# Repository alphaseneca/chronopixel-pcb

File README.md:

# ChronoPixel PCB ⏳🔌

Hardware design repository for **ChronoPixel** — an open-source, gravity-sensing digital sand timer and smart pixel hourglass. Contains the KiCad schematics, PCB layout, manufacturing outputs, and assembly files.

---

## 📸 3D Board Previews

<div align="center">

</div>

---

## ⏳ How the Hardware Powers the Digital Sand Timer

The PCB is architected specifically around the physical interactions of a traditional hourglass:

1. **Dual Hourglass Chambers (Dual MAX7219 + 2× 8×8 LED Matrices)**:
   The two stacked LED matrices represent the upper and lower bulbs of the hourglass. Individual pixel "sand grains" trickle through the center constriction from the top chamber to accumulate in the bottom chamber.
2. **Gravity & Tilt Tracking (Bosch BMI323 6-Axis IMU)**:
   An onboard 6-axis accelerometer/gyroscope continuously measures the gravity vector. When you turn the device upside down, tilt it, or lay it flat, the physics engine responds in real-time, causing virtual sand grains to tumble and settle naturally.
3. **True Cordless Hourglass Operation (TI BQ24075)**:
   Equipped with autonomous dynamic power-path management and integrated Li-Ion/Li-Po charging. The device can be picked up, flipped, and set down on a desk cordlessly just like a classic sand glass.
4. **Time's Up Audio Alert (MLT-7525 Buzzer)**:
   An onboard SMD buzzer sounds a chime or alarm tone the instant the final grain of sand drops.
5. **Smart Connectivity (ESP-12F Wi-Fi SoC)**:
   Enables setting timer presets (e.g. 25-minute Pomodoro, 5-minute break, tea steeping, custom countdowns) via a local web interface or mobile device.

---

## ⚡ Hardware Architecture & Key Components

| Subsystem | Component | Package / Footprint | Description / Role |
| :--- | :--- | :--- | :--- |
| **Microcontroller** | **ESP-12F** | SMD Module | ESP8266 Wi-Fi SoC with on-board PCB antenna |
| **Display Drivers** | **2× MAX7219EWG** | SOIC-24 | Serially interfaced LED matrix drivers |
| **Hourglass Chambers** | **2× SZ421288N/64** | Through-hole | Stacked 8×8 LED dot matrix modules for sand grains |
| **Motion Sensor** | **BMI323** | LGA-14 | Bosch 6-axis IMU (accelerometer + gyroscope) for gravity tracking |
| **Power-Path / Charger** | **BQ24075RGTR** | QFN-16 | Dynamic power-path management & Li-Ion battery charger |
| **Voltage Regulator** | **TLV73333PDBVR** | SOT-23-5 | High-efficiency 3.3V 300mA low-dropout regulator |
| **USB Interface** | **USB Type-C (16-pin)** | SMD / Hybrid | 5V DC power & battery charging (with CC pulldowns) |
| **Battery Connector** | **SM02B-SRSS-TB** | SMD 1.0mm pitch | 2-pin JST connector for 3.7V Li-Po / Li-Ion battery |
| **Audio Feedback** | **MLT-7525** | SMD 7.5×7.5mm | Magnetic buzzer for alarm chimes when sand runs out |
| **Programming Header** | **BM06B-SRSS-TB** | SMD 1.0mm pitch | 6-pin interface (UART, RST, GPIO0, 3V3, GND) |
| **Control Switch** | **B3U-1000P** | Ultra-small SMD | Hardware input / wake tactile switch |

---

## 🔋 Power Architecture

- **Seamless Cordless & Desktop Use**: Operates cordlessly on a rechargeable 3.7V Li-Po/Li-Ion battery or plugged in over USB Type-C.
- **Dynamic Power-Path Management (TI BQ24075)**: 
  - When USB is connected, system loads are powered directly from the USB supply while simultaneously charging the battery.
  - Automatically supplements system current from the battery if load exceeds USB current limits.
  - Instantaneous, glitch-free switchover to battery power when unseated or picked up.
- **Clean 3.3V Rail**: Powered by a low-noise TI TLV73333 LDO ensuring stable power for the ESP8266 Wi-Fi bursts and low-noise readings from the BMI323 IMU.

---

## 📁 Repository Structure

```text
chronopixel-pcb/
├── chronopixel-pcb.kicad_pro    # KiCad project file
├── chronopixel-pcb.kicad_sch    # Schematic design file
├── chronopixel-pcb.kicad_pcb    # 2-layer PCB layout
├── chronopixel-pcb.kicad_prl    # KiCad local settings
├── .kiforge.json                # KiForge export configuration
└── kiforge/                     # Automated manufacturing & inspection artifacts
    ├── chronopixel-pcb_v0.1.0_gerbers.zip   # Fabrication Gerbers & drill files
    ├── chronopixel-pcb_v0.1.0_bom.csv       # Complete bill of materials
    ├── chronopixel-pcb_v0.1.0_bom_jlc.csv   # JLCPCB formatted BOM (with LCSC C-IDs)
    ├── chronopixel-pcb_v0.1.0_cpl_jlc.csv   # JLCPCB pick-and-place (CPL/POS) file
    ├── chronopixel-pcb_v0.1.0_ibom.html     # Interactive HTML BOM for easy hand assembly
    ├── chronopixel-pcb_v0.1.0_sch.pdf       # Printable schematic PDF
    ├── chronopixel-pcb_v0.1.0.step          # Complete 3D STEP CAD model
    ├── chronopixel-pcb_v0.1.0_3d_front.png  # 3D render front
    └── chronopixel-pcb_v0.1.0_3d_back.png   # 3D render back
```

---

## 🏭 Fabrication & Assembly

All components have been selected with readily available LCSC part numbers for automated SMD assembly via JLCPCB or manual soldering:

- **Order PCB**: Submit `kiforge/chronopixel-pcb_v0.1.0_gerbers.zip` to your preferred PCB fabricator.
- **SMT Assembly**: Upload `kiforge/chronopixel-pcb_v0.1.0_bom_jlc.csv` and `kiforge/chronopixel-pcb_v0.1.0_cpl_jlc.csv`.
- **Manual Hand Assembly**: Open `kiforge/chronopixel-pcb_v0.1.0_ibom.html` in any web browser to highlight component locations and references interactively.

---

## 📜 License

This hardware project is open source and licensed under the [MIT License](LICENSE).

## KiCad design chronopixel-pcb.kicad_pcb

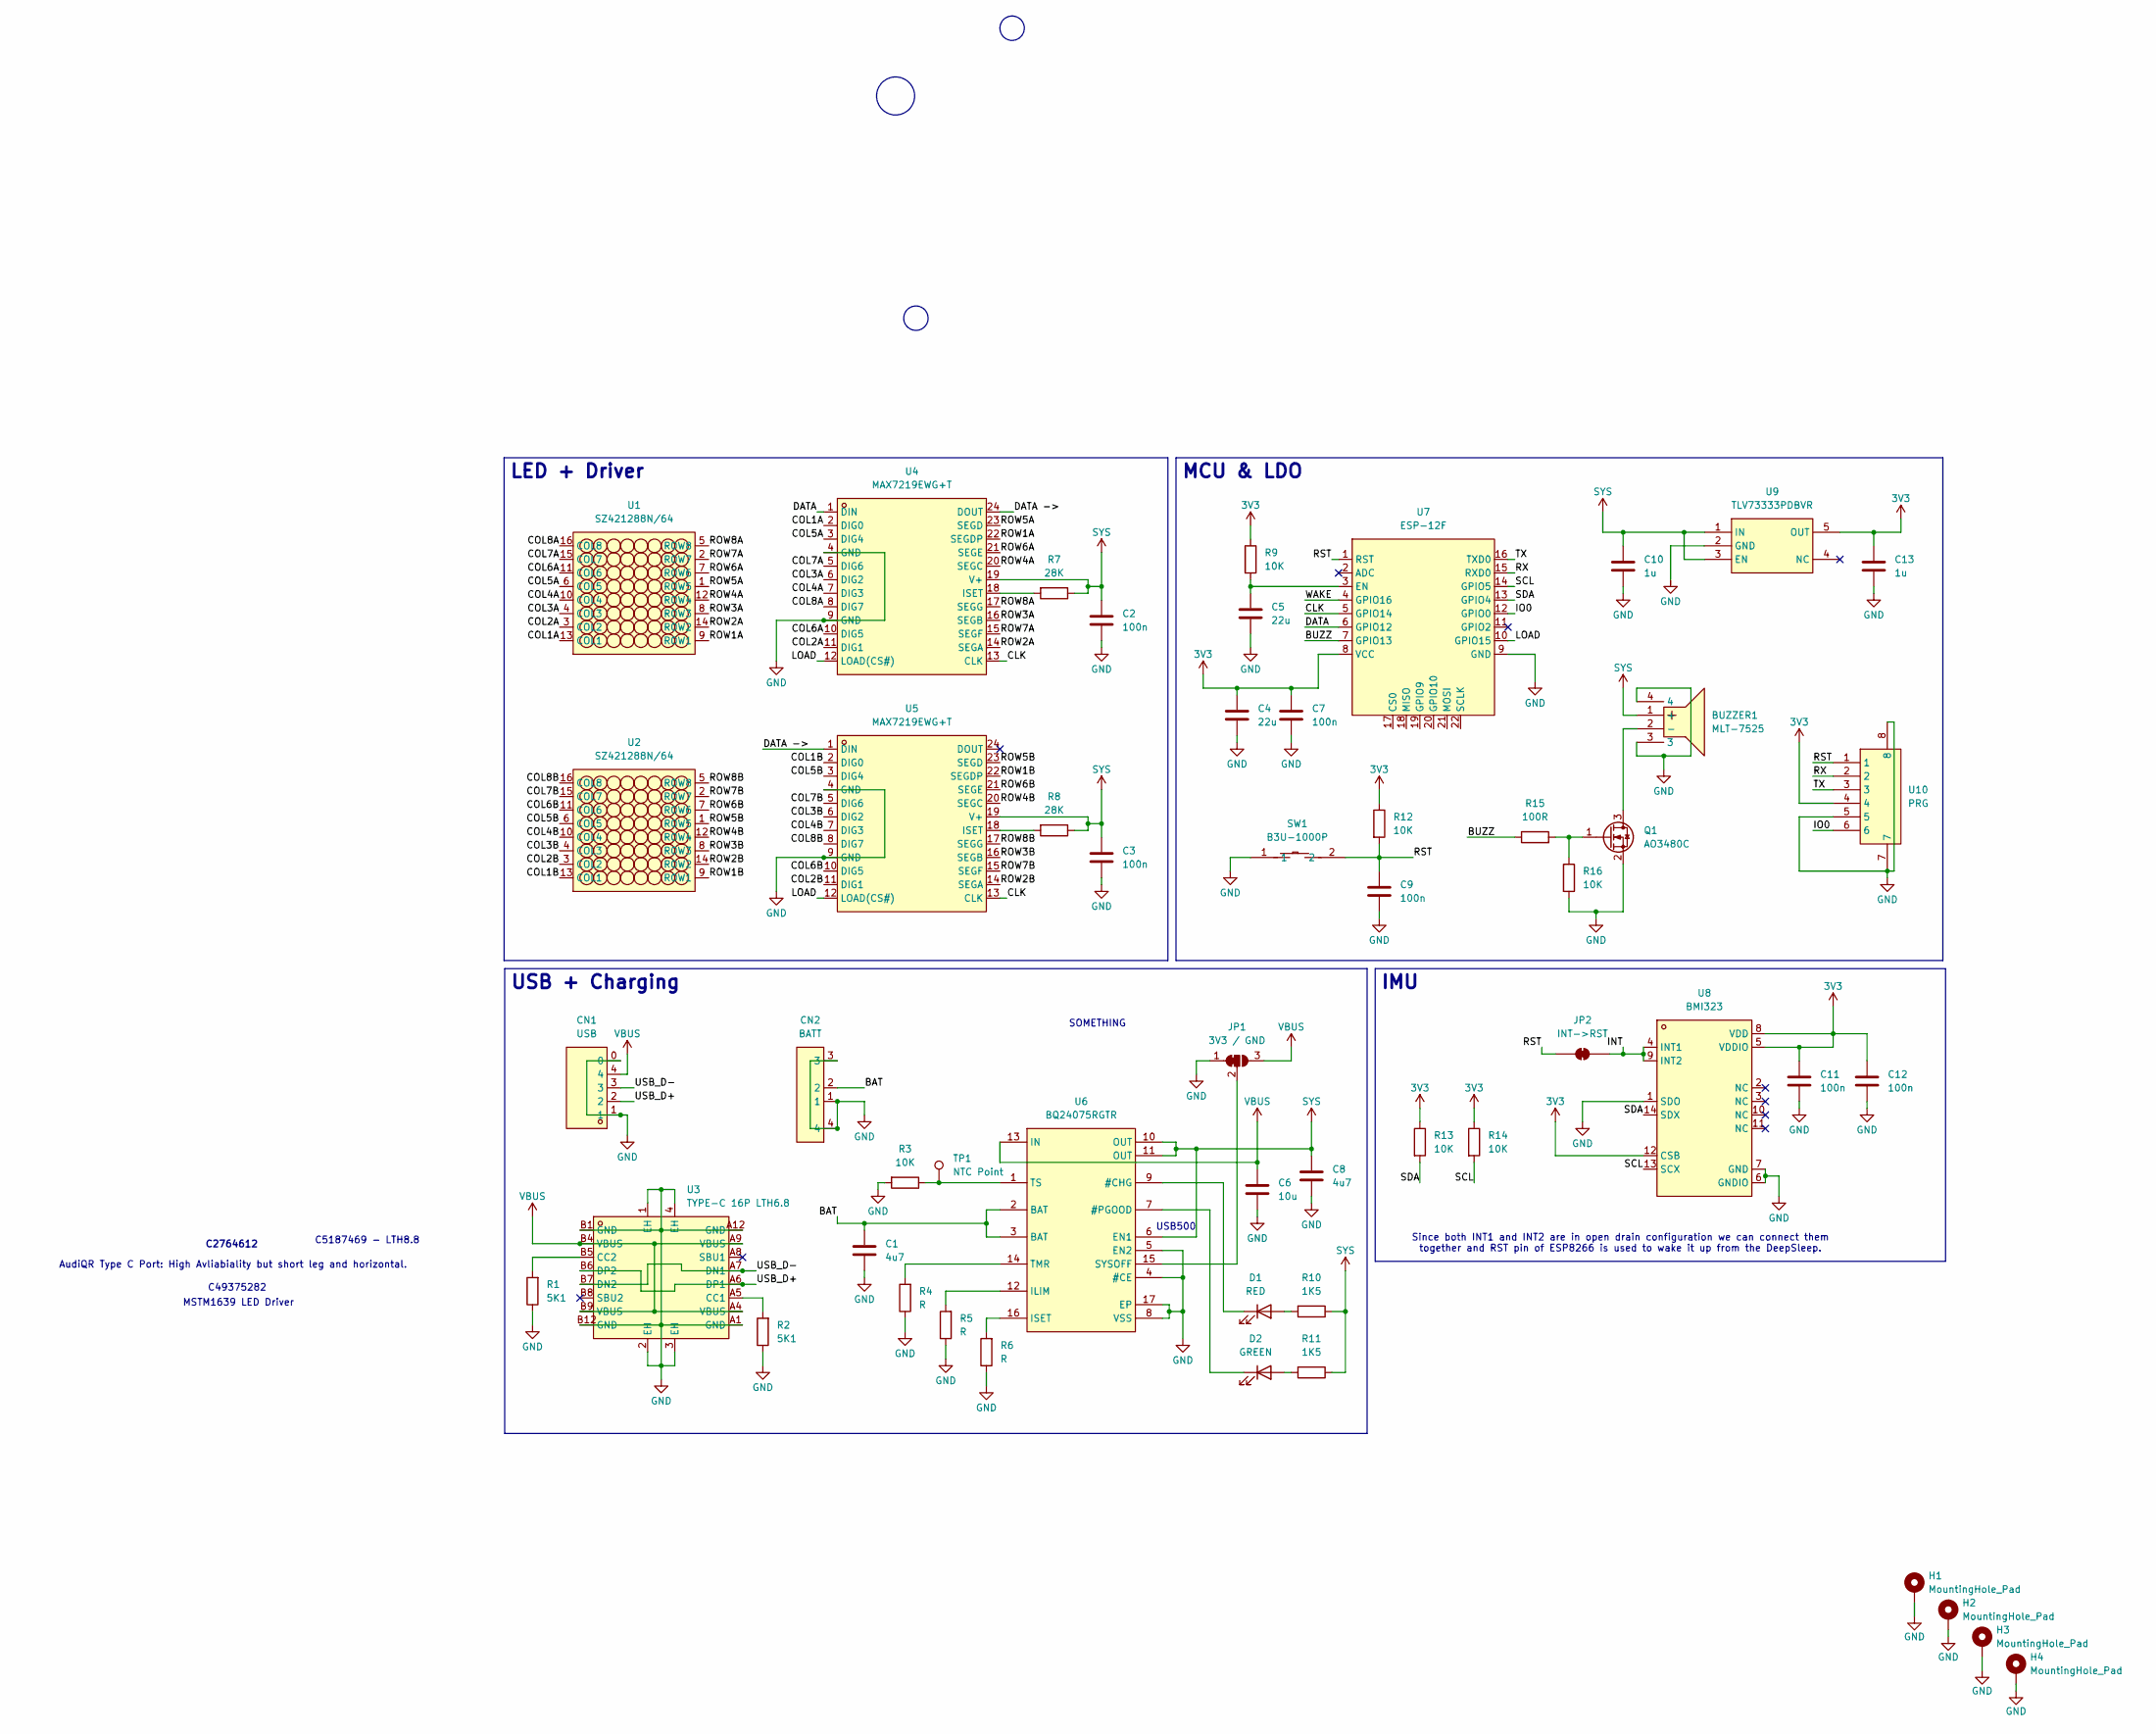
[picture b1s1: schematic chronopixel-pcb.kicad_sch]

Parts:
BUZZER1: MLT-7525; BUZ-SMD_4P-L7.5-W7.5-P7.59-TL; MPN MLT-7525
C1, C8: 4u7; C_0805_2012Metric; MPN CL21A475KAQNNNE
C2, C3, C7, C9, C11, C12: 100n; C_0603_1608Metric; MPN CL10B104KB8NNNC
C4, C5: 22u; C_0805_2012Metric; MPN CL21A226MAYNNNE
C6: 10u; C_0805_2012Metric; MPN CL21A106KAYNNNE
C10, C13: 1u; C_0805_2012Metric; MPN CL21B105KBFNNNE
CN1: USB; CONN-SMD_BM04B-SRSS-TB; MPN BM04B-SRSS-TB(LF)(SN)
CN2: BATT; CONN-SMD_2P-P1.00_SM02B-SRSS-TB-LF-SN; MPN SM02B-SRSS-TB(LF)(SN)
D1: RED; LED_0603_1608Metric; MPN XL-1608SURC-06
D2: GREEN; LED_0603_1608Metric; MPN XL-1608UGC-04
H1, H2, H3, H4: MountingHole_Pad; MountingHole_2.2mm_M2_Pad_Via
JP1: 3V3 / GND; SolderJumper-3_P1.3mm_Bridged12_RoundedPad1.0x1.5mm
JP2: INT->RST; SolderJumper-2_P1.3mm_Bridged_RoundedPad1.0x1.5mm
Q1: AO3480C; SOT-23; MPN AO3400A
R1, R2: 5K1; R_0603_1608Metric; MPN RC0603FR-075K1L
R3, R9, R12, R13, R14, R16: 10K; R_0603_1608Metric; MPN RC0603FR-0710KL
R4, R5, R6: R; R_0603_1608Metric
R7, R8: 28K; R_0603_1608Metric; MPN RC0603FR-0728KL
R10, R11: 1K5; R_0603_1608Metric; MPN RC0603FR-071K5L
R15: 100R; R_0603_1608Metric; MPN RC0603FR-07100RL
SW1: B3U-1000P; KEY-SMD_B3U-1000PM; MPN B3U-1000P
TP1: NTC Point; TestPoint_Pad_D1.0mm
U1, U2: SZ421288N/64; LED-SEG-TH_SZ421288N-64; MPN SZ421288N/64
U3: TYPE-C 16P LTH6.8; USB-C-SMD_TYPE-C-16P-LTH6.8; MPN TYPE-C 16P LTH6.8
U4, U5: MAX7219EWG+T; SOIC-24_L15.4-W7.5-P1.27-LS10.3-BL; MPN MAX7219EWG+T
U6: BQ24075RGTR; QFN-16_L3.0-W3.0-P0.50-TL-EP1.7; MPN BQ24075RGTR
U7: ESP-12F; ESP-12E; MPN ESP-12F(ESP8266MOD)
U8: BMI323; LGA-14_L3.0-W2.5-P0.50-TL_QMI8658A; MPN BMI323
U9: TLV73333PDBVR; SOT-23-5_L3.0-W1.7-P0.95-LS2.8-BR; MPN TLV73333PDBVR
U10: PRG; CONN-SMD-6P-P1.00_BM06B-SRSS-TB-LF-SN; MPN BM06B-SRSS-TB(LF)(SN)

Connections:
3V3: C4.1, C7.1, C11.1, C12.1, C13.1, R9.1, R12.1, R13.1, R14.1, U7.8 (VCC), U8.5 (VDDIO), U8.8 (VDD), U8.12 (CSB), U9.5 (OUT), U10.4
/BAT: C1.1, CN2.2, U6.2 (BAT), U6.3 (BAT)
/BUZZ: R15.1, U7.7 (GPIO13)
/CLK: U4.13 (CLK), U5.13 (CLK), U7.5 (GPIO14)
/COL1A: U1.13 (COL1), U4.2 (DIG0)
/COL1B: U2.13 (COL1), U5.2 (DIG0)
/COL2A: U1.3 (COL2), U4.11 (DIG1)
/COL2B: U2.3 (COL2), U5.11 (DIG1)
/COL3A: U1.4 (COL3), U4.6 (DIG2)
/COL3B: U2.4 (COL3), U5.6 (DIG2)
/COL4A: U1.10 (COL4), U4.7 (DIG3)
/COL4B: U2.10 (COL4), U5.7 (DIG3)
/COL5A: U1.6 (COL5), U4.3 (DIG4)
/COL5B: U2.6 (COL5), U5.3 (DIG4)
/COL6A: U1.11 (COL6), U4.10 (DIG5)
/COL6B: U2.11 (COL6), U5.10 (DIG5)
/COL7A: U1.15 (COL7), U4.5 (DIG6)
/COL7B: U2.15 (COL7), U5.5 (DIG6)
/COL8A: U1.16 (COL8), U4.8 (DIG7)
/COL8B: U2.16 (COL8), U5.8 (DIG7)
/DATA: U4.1 (DIN), U7.6 (GPIO12)
/DATA ->: U4.24 (DOUT), U5.1 (DIN)
/INT: JP2.2 (B), U8.4 (INT1), U8.9 (INT2)
/IO0: U7.12 (GPIO0), U10.6
/LOAD: U4.12 (LOAD(CS#)), U5.12 (LOAD(CS#)), U7.10 (GPIO15)
/ROW1A: U1.9 (ROW1), U4.22 (SEGDP)
/ROW1B: U2.9 (ROW1), U5.22 (SEGDP)
/ROW2A: U1.14 (ROW2), U4.14 (SEGA)
/ROW2B: U2.14 (ROW2), U5.14 (SEGA)
/ROW3A: U1.8 (ROW3), U4.16 (SEGB)
/ROW3B: U2.8 (ROW3), U5.16 (SEGB)
/ROW4A: U1.12 (ROW4), U4.20 (SEGC)
/ROW4B: U2.12 (ROW4), U5.20 (SEGC)
/ROW5A: U1.1 (ROW5), U4.23 (SEGD)
/ROW5B: U2.1 (ROW5), U5.23 (SEGD)
/ROW6A: U1.7 (ROW6), U4.21 (SEGE)
/ROW6B: U2.7 (ROW6), U5.21 (SEGE)
/ROW7A: U1.2 (ROW7), U4.15 (SEGF)
/ROW7B: U2.2 (ROW7), U5.15 (SEGF)
/ROW8A: U1.5 (ROW8), U4.17 (SEGG)
/ROW8B: U2.5 (ROW8), U5.17 (SEGG)
/RST: C9.1, JP2.1 (A), R12.2, SW1.2, U7.1 (RST), U10.1
/RX: U7.15 (RXD0), U10.2
/SCL: R14.2, U7.14 (GPIO5), U8.13 (SCX)
/SDA: R13.2, U7.13 (GPIO4), U8.14 (SDX)
/TX: U7.16 (TXD0), U10.3
/USB_D+: CN1.2, U3.A6 (DP1), U3.B6 (DP2)
/USB_D-: CN1.3, U3.A7 (DN1), U3.B7 (DN2)
/WAKE: U7.4 (GPIO16)
GND: BUZZER1.3, BUZZER1.4, C1.2, C2.2, C3.2, C4.2, C5.2, C6.2, C7.2, C8.2, C9.2, C10.2, C11.2, C12.2, C13.2, CN1.0, CN1.1, CN2.1, CN2.3, CN2.4, H1.1 (1_1), H2.1 (1_1), H3.1 (1_1), H4.1 (1_1), JP1.1 (A), Q1.2 (S), R1.1, R2.1, R3.2, R4.1, R5.1, R6.1, R16.2, SW1.1, U3.1 (EH), U3.2 (EH), U3.3 (EH), U3.4 (EH), U3.A1 (GND), U3.A12 (GND), U3.B1 (GND), U3.B12 (GND), U4.4 (GND), U4.9 (GND), U5.4 (GND), U5.9 (GND), U6.4 (#CE), U6.5 (EN2), U6.8 (VSS), U6.17 (EP), U7.9 (GND), U8.1 (SDO), U8.6 (GNDIO), U8.7 (GND), U9.2 (GND), U10.5, U10.7, U10.8
unnamed: BUZZER1.2 (-), Q1.3 (D)
unnamed: D1.2 (A), R10.2
unnamed: D1.1 (K), U6.9 (#CHG)
unnamed: D2.2 (A), R11.2
unnamed: D2.1 (K), U6.7 (#PGOOD)
unnamed: JP1.2 (C), U6.15 (SYSOFF)
unnamed: Q1.1 (G), R15.2, R16.1
unnamed: R2.2, U3.A5 (CC1)
unnamed: R1.2, U3.B5 (CC2)
unnamed: R7.2, U4.18 (ISET)
unnamed: R8.2, U5.18 (ISET)
unnamed: R5.2, U6.12 (ILIM)
unnamed: R6.2, U6.16 (ISET)
unnamed: R4.2, U6.14 (TMR)
unnamed: R3.1, TP1.1 (1_1), U6.1 (TS)
unnamed: C5.1, R9.2, U7.3 (EN)
SYS: BUZZER1.1 (+), C2.1, C3.1, C8.1, C10.1, R7.1, R8.1, R10.1, R11.1, U4.19 (V+), U5.19 (V+), U6.6 (EN1), U6.10 (OUT), U6.11 (OUT), U9.1 (IN), U9.3 (EN)
VBUS: C6.1, CN1.4, JP1.3 (B), U3.A4 (VBUS), U3.A9 (VBUS), U3.B4 (VBUS), U3.B9 (VBUS), U6.13 (IN)

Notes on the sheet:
MSTM1639 LED Driver
USB500
AudiQR Type C Port: High Avliabiality but short leg and horizontal.
C2764612
SOMETHING
C49375282
Since both INT1 and INT2 are in open drain configuration we can connect them together and RST pin of ESP8266 is used to wake it up from the DeepSleep.
C5187469 - LTH8.8
IMU
LED + Driver
USB + Charging
MCU & LDO

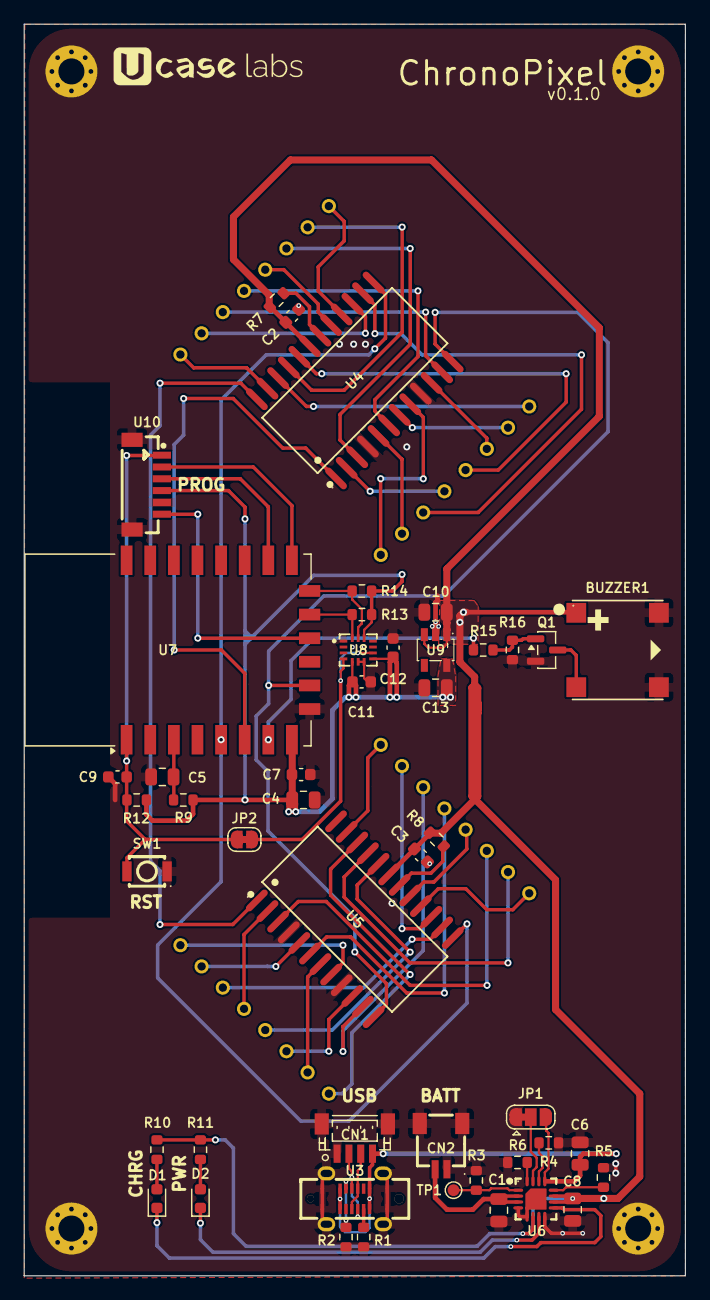
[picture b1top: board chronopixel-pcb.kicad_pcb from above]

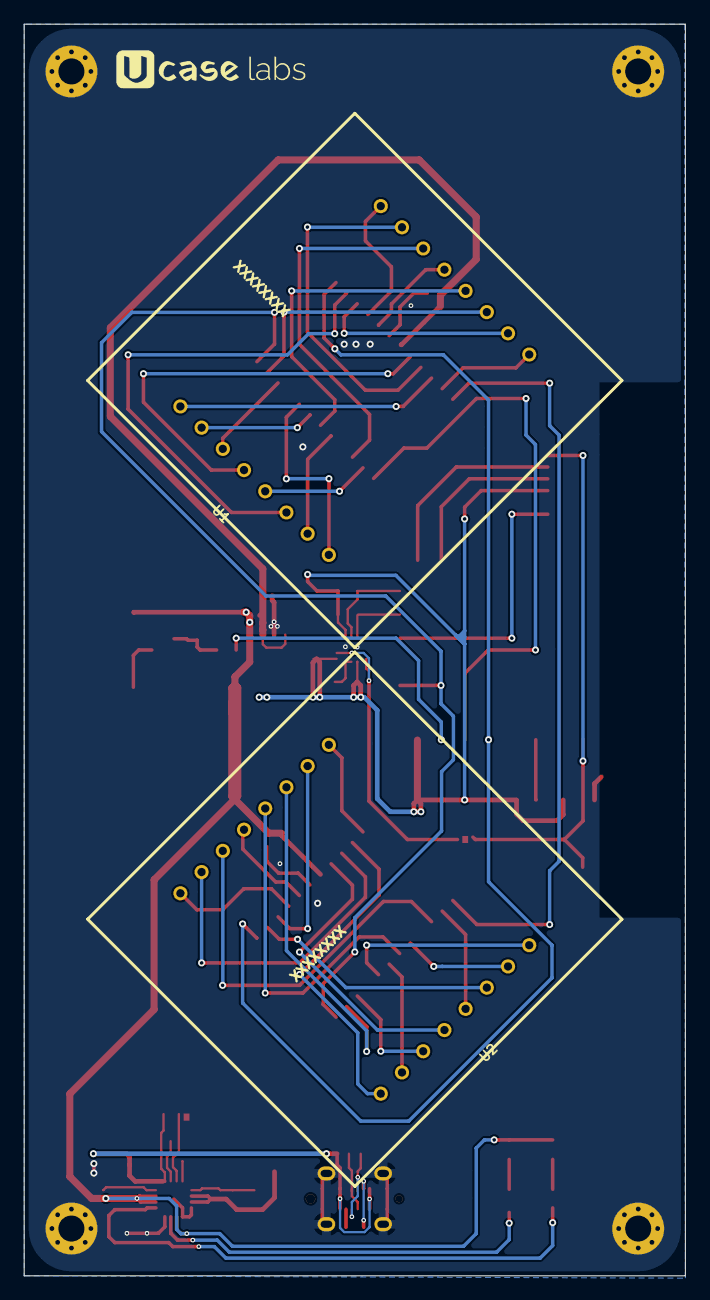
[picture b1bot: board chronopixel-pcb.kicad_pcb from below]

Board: 2 copper layers, 56.0 x 106.0 mm, 53 parts (2 on the bottom side), 67 nets.

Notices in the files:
README.md:
License: MIT
